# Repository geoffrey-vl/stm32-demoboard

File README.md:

# IO shield for Nucleo boards

This repo contains the source files to make an add-on shield for STM32 Nulceo boards that contains 8 buttons, 8 outputs LEDs and 2 status LEDs.

Note that I haven't verified the functionality of this board.

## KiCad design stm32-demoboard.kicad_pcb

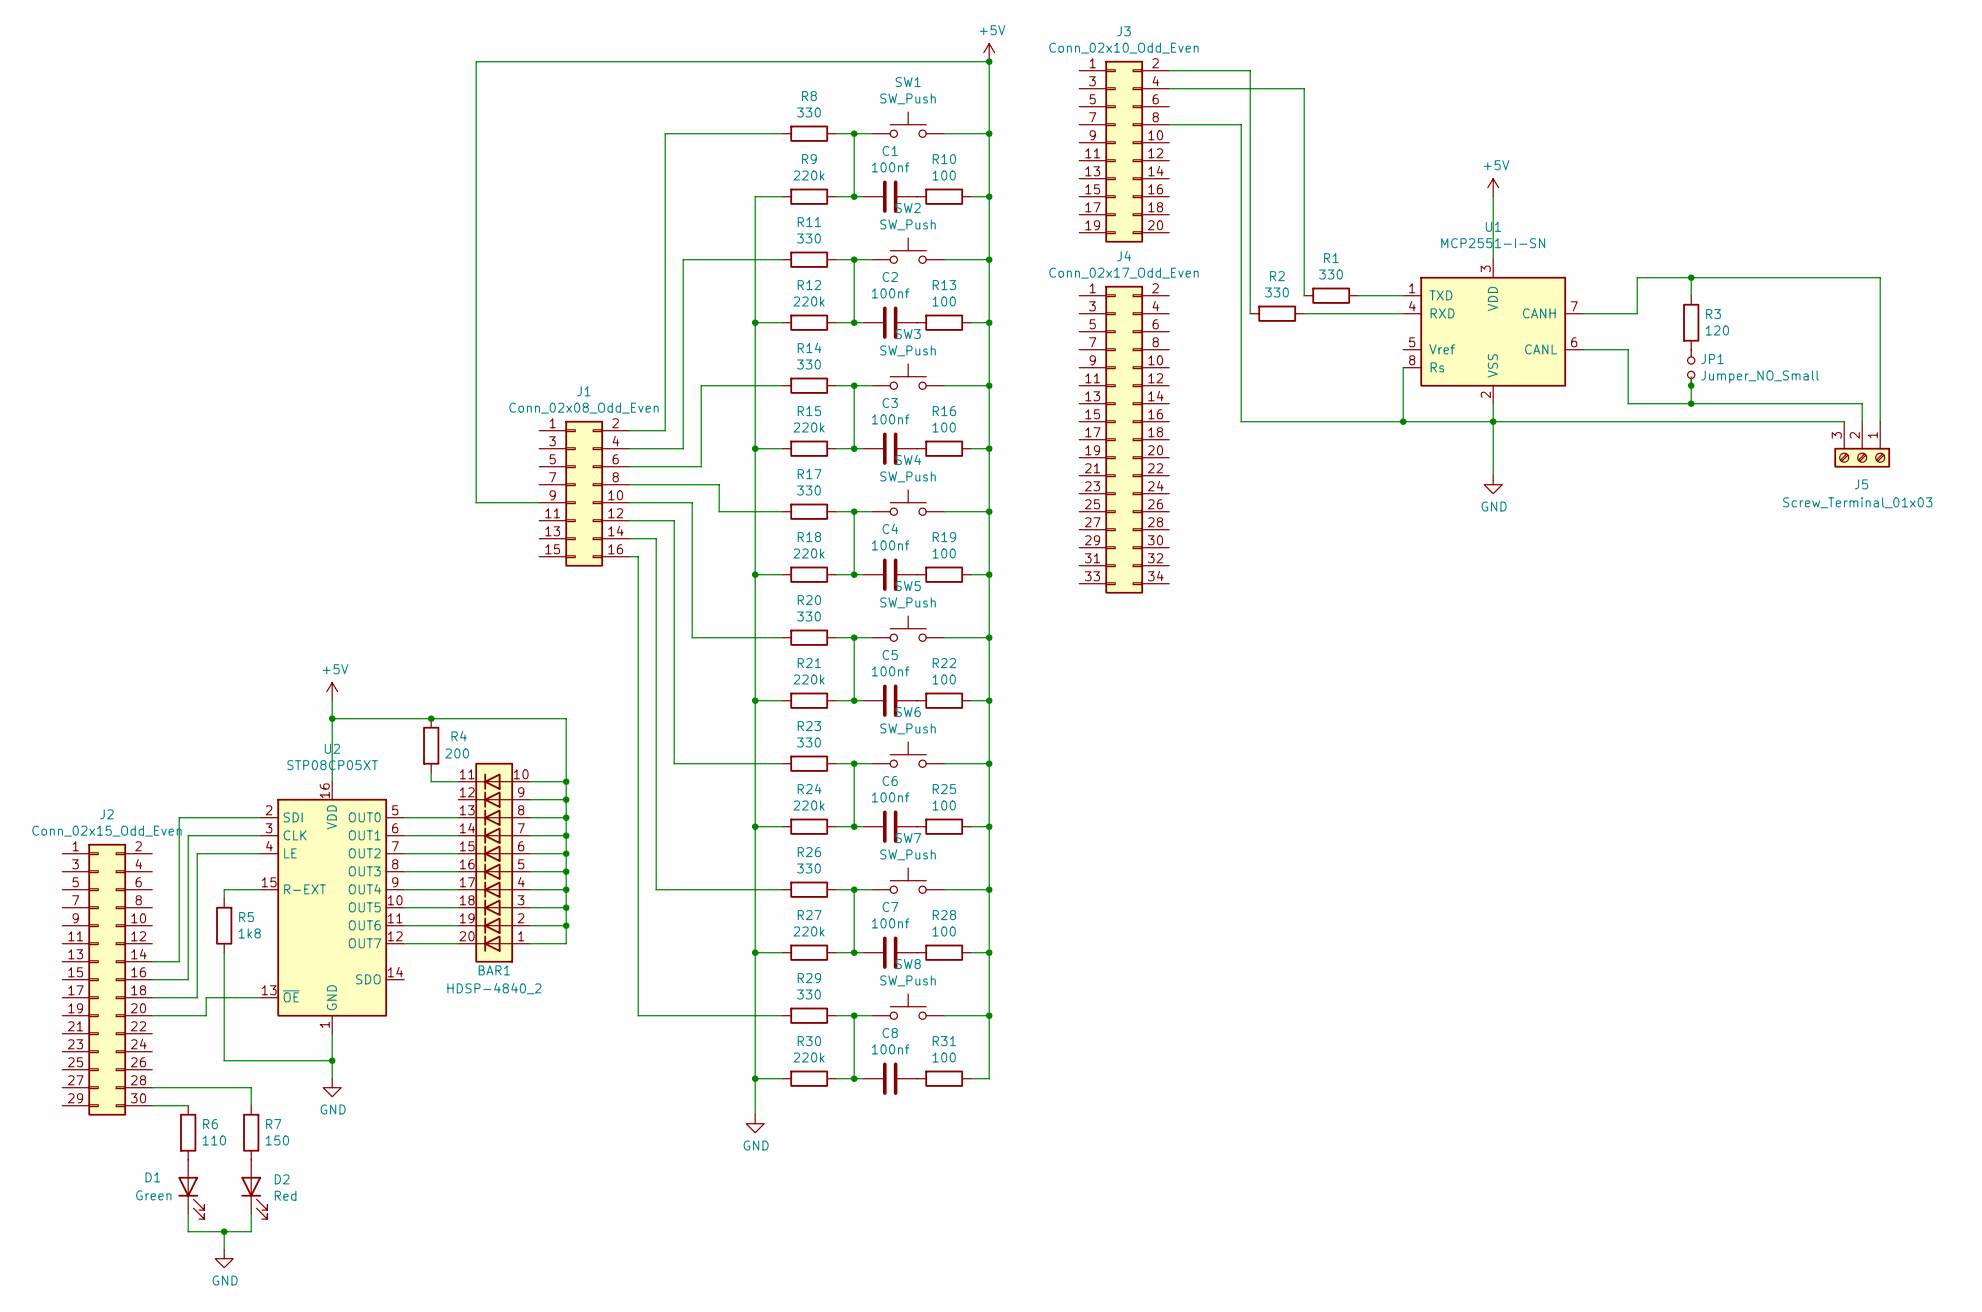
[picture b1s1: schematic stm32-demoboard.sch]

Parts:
BAR1: HDSP-4840_2; HDSP-4840
C1, C2, C3, C4, C5, C6, C7, C8: 100nf; CP_Radial_D5.0mm_P2.50mm
D1: Green; LED_D3.0mm
D2: Red; LED_D3.0mm
J1: Conn_02x08_Odd_Even; PinSocket_2x08_P2.54mm_Vertical
J2: Conn_02x15_Odd_Even; PinSocket_2x15_P2.54mm_Vertical
J3: Conn_02x10_Odd_Even; PinSocket_2x10_P2.54mm_Vertical
J4: Conn_02x17_Odd_Even; PinSocket_2x17_P2.54mm_Vertical
J5: Screw_Terminal_01x03; PhoenixContact_MCV_1,5_3-G-3.5_1x03_P3.50mm_Vertical
JP1: Jumper_NO_Small; PinHeader_1x02_P2.54mm_Vertical
R1, R2, R8, R11, R14, R17, R20, R23, R26, R29: 330; R_Axial_DIN0204_L3.6mm_D1.6mm_P5.08mm_Horizontal
R3: 120; R_Axial_DIN0204_L3.6mm_D1.6mm_P5.08mm_Horizontal
R4: 200; R_Axial_DIN0204_L3.6mm_D1.6mm_P5.08mm_Horizontal
R5: 1k8; R_Axial_DIN0204_L3.6mm_D1.6mm_P5.08mm_Horizontal
R6: 110; R_Axial_DIN0204_L3.6mm_D1.6mm_P5.08mm_Horizontal
R7: 150; R_Axial_DIN0204_L3.6mm_D1.6mm_P5.08mm_Horizontal
R9, R12, R15, R18, R21, R24, R27, R30: 220k; R_Axial_DIN0204_L3.6mm_D1.6mm_P5.08mm_Horizontal
R10, R13, R16, R19, R22, R25, R28, R31: 100; R_Axial_DIN0204_L3.6mm_D1.6mm_P5.08mm_Horizontal
SW1, SW2, SW3, SW4, SW5, SW6, SW7, SW8: SW_Push; SW_SPST_Omron_B3FS-100xP
U1: MCP2551-I-SN; SOIC-8_3.9x4.9mm_P1.27mm
U2: STP08CP05XT; HTSSOP-16-1EP_4.4x5mm_P0.65mm_EP3x3mm

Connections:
+5V: BAR1.1 (A), BAR1.2 (A), BAR1.3 (A), BAR1.4 (A), BAR1.5 (A), BAR1.6 (A), BAR1.7 (A), BAR1.8 (A), BAR1.9 (A), BAR1.10 (A), J1.9, R4.1, R10.1, R13.1, R16.1, R19.1, R22.1, R25.1, R28.1, R31.1, SW1.2, SW2.2, SW3.2, SW4.2, SW5.2, SW6.2, SW7.2, SW8.2, U1.3 (VDD), U2.16 (VDD)
GND: D1.1 (K), D2.1 (K), J3.8, J5.3, R5.1, R9.2, R12.2, R15.2, R18.2, R21.2, R24.2, R27.2, R30.2, U1.2 (VSS), U1.8 (Rs), U2.1 (GND), U2.17 (GND)
unnamed: BAR1.11 (K), R4.2
unnamed: BAR1.13 (K), U2.5 (OUT0)
unnamed: BAR1.14 (K), U2.6 (OUT1)
unnamed: BAR1.15 (K), U2.7 (OUT2)
unnamed: BAR1.16 (K), U2.8 (OUT3)
unnamed: BAR1.17 (K), U2.9 (OUT4)
unnamed: BAR1.18 (K), U2.10 (OUT5)
unnamed: BAR1.19 (K), U2.11 (OUT6)
unnamed: BAR1.20 (K), U2.12 (OUT7)
unnamed: C1.1, R10.2
unnamed: C1.2, R8.1, R9.1, SW1.1
unnamed: C2.1, R13.2
unnamed: C2.2, R11.1, R12.1, SW2.1
unnamed: C3.1, R16.2
unnamed: C3.2, R14.1, R15.1, SW3.1
unnamed: C4.1, R19.2
unnamed: C4.2, R17.1, R18.1, SW4.1
unnamed: C5.1, R22.2
unnamed: C5.2, R20.1, R21.1, SW5.1
unnamed: C6.1, R25.2
unnamed: C6.2, R23.1, R24.1, SW6.1
unnamed: C7.1, R28.2
unnamed: C7.2, R26.1, R27.1, SW7.1
unnamed: C8.1, R31.2
unnamed: C8.2, R29.1, R30.1, SW8.1
unnamed: D1.2 (A), R6.2
unnamed: D2.2 (A), R7.1
unnamed: J1.2, R8.2
unnamed: J1.4, R11.2
unnamed: J1.6, R14.2
unnamed: J1.8, R17.2
unnamed: J1.10, R20.2
unnamed: J1.12, R23.2
unnamed: J1.14, R26.2
unnamed: J1.16, R29.2
unnamed: J2.14, U2.2 (SDI)
unnamed: J2.16, U2.3 (CLK)
unnamed: J2.18, U2.4 (LE)
unnamed: J2.20, U2.13 (~OE)
unnamed: J2.28, R7.2
unnamed: J2.30, R6.1
unnamed: J3.2, R2.2
unnamed: J3.4, R1.2
unnamed: J5.1, R3.1, U1.7 (CANH)
unnamed: J5.2, JP1.1, U1.6 (CANL)
unnamed: JP1.2, R3.2
unnamed: R1.1, U1.1 (TXD)
unnamed: R2.1, U1.4 (RXD)
unnamed: R5.2, U2.15 (R-EXT)

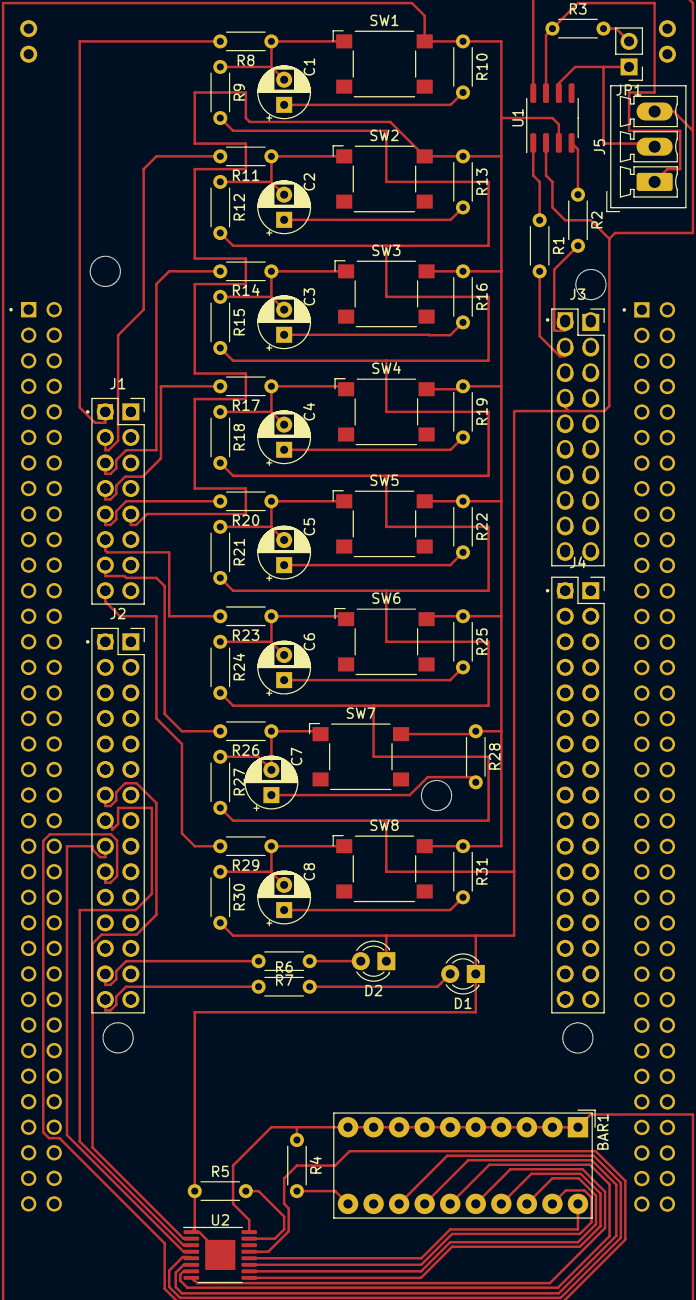
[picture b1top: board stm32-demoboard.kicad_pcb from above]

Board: 2 copper layers, 58 parts (0 on the bottom side), 51 nets.

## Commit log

2021-05-19 everything wired up, DRC fails
